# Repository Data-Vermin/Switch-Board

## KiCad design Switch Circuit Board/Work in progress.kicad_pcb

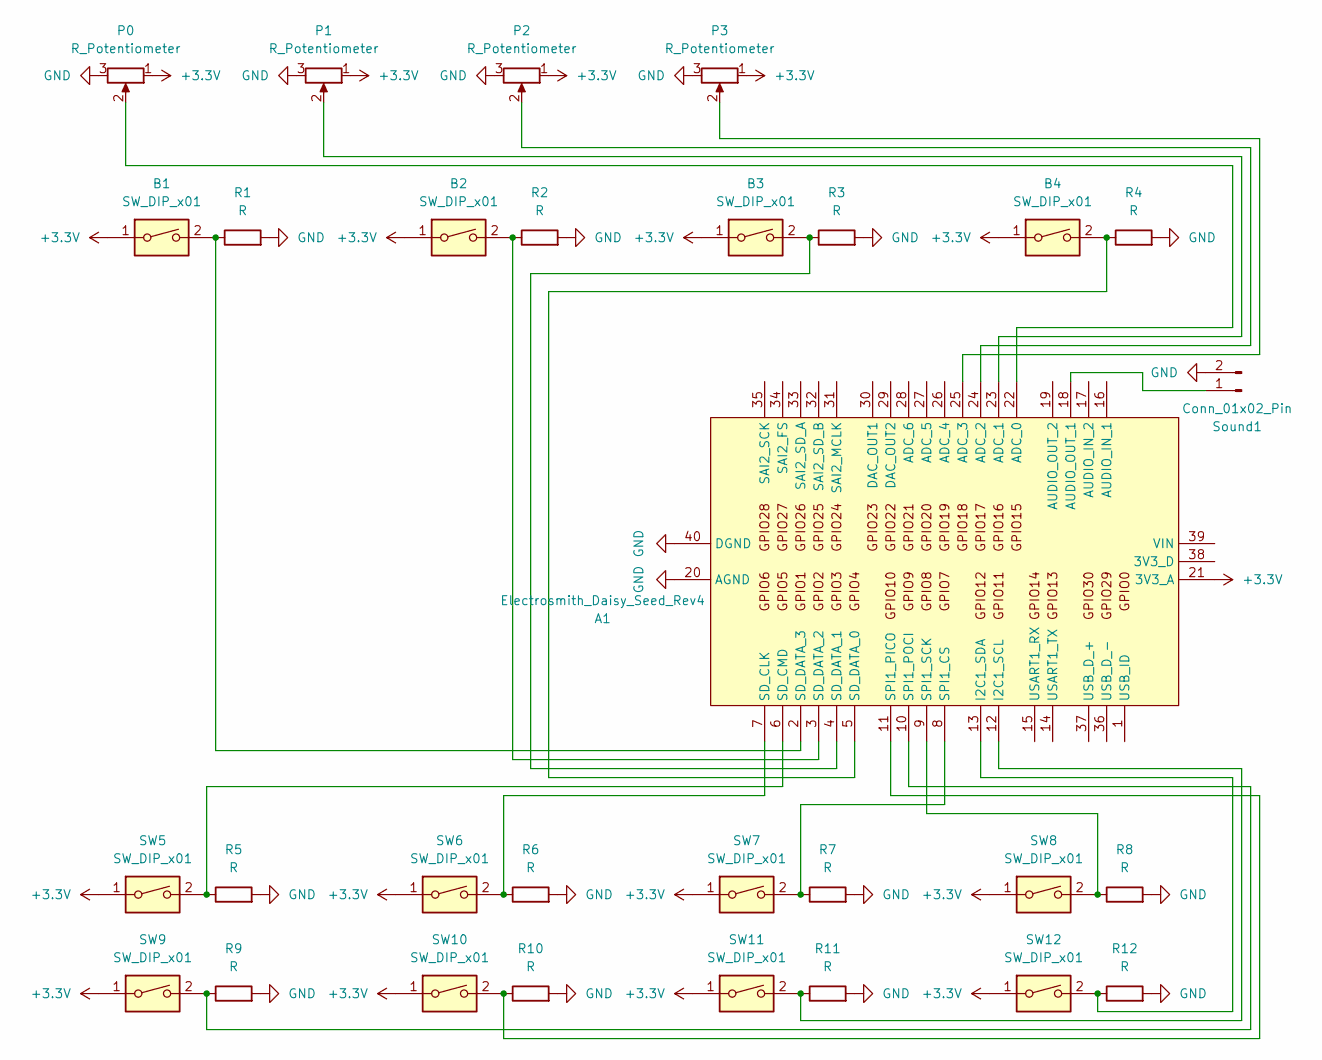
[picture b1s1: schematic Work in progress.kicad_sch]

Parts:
A1: Electrosmith_Daisy_Seed_Rev4; Electrosmith_Daisy_Seed
B1, B2, B3, B4: SW_DIP_x01; PinHeader_1x02_P2.54mm_Vertical
P0, P1, P2, P3: R_Potentiometer; PinHeader_1x03_P2.54mm_Vertical
R1, R2, R3, R4, R5, R6, R7, R8, R9, R10, R11, R12: R; R_Axial_DIN0204_L3.6mm_D1.6mm_P7.62mm_Horizontal
SW5, SW6, SW7, SW8, SW9, SW10, SW11, SW12: SW_DIP_x01; PinHeader_1x02_P2.54mm_Vertical
Sound1: Conn_01x02_Pin; PinHeader_1x02_P2.54mm_Vertical

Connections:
+3.3V: A1.21 (3V3_A), B1.1, B2.1, B3.1, B4.1, P0.1, P1.1, P2.1, P3.1, SW5.1, SW6.1, SW7.1, SW8.1, SW9.1, SW10.1, SW11.1, SW12.1
GND: A1.20 (AGND), A1.40 (DGND), P0.3, P1.3, P2.3, P3.3, R1.2, R2.2, R3.2, R4.2, R5.2, R6.2, R7.2, R8.2, R9.2, R10.2, R11.2, R12.2, Sound1.2
unnamed: A1.22 (ADC_0), P0.2
unnamed: A1.23 (ADC_1), P1.2
unnamed: A1.24 (ADC_2), P2.2
unnamed: A1.25 (ADC_3), P3.2
unnamed: A1.18 (AUDIO_OUT_1), Sound1.1
unnamed: A1.12 (I2C1_SCL), R11.1, SW11.2
unnamed: A1.13 (I2C1_SDA), R12.1, SW12.2
unnamed: A1.7 (SD_CLK), R6.1, SW6.2
unnamed: A1.6 (SD_CMD), R5.1, SW5.2
unnamed: A1.5 (SD_DATA_0), B4.2, R4.1
unnamed: A1.4 (SD_DATA_1), B3.2, R3.1
unnamed: A1.3 (SD_DATA_2), B2.2, R2.1
unnamed: A1.2 (SD_DATA_3), B1.2, R1.1
unnamed: A1.8 (SPI1_CS), R7.1, SW7.2
unnamed: A1.11 (SPI1_PICO), R10.1, SW10.2
unnamed: A1.10 (SPI1_POCI), R9.1, SW9.2
unnamed: A1.9 (SPI1_SCK), R8.1, SW8.2

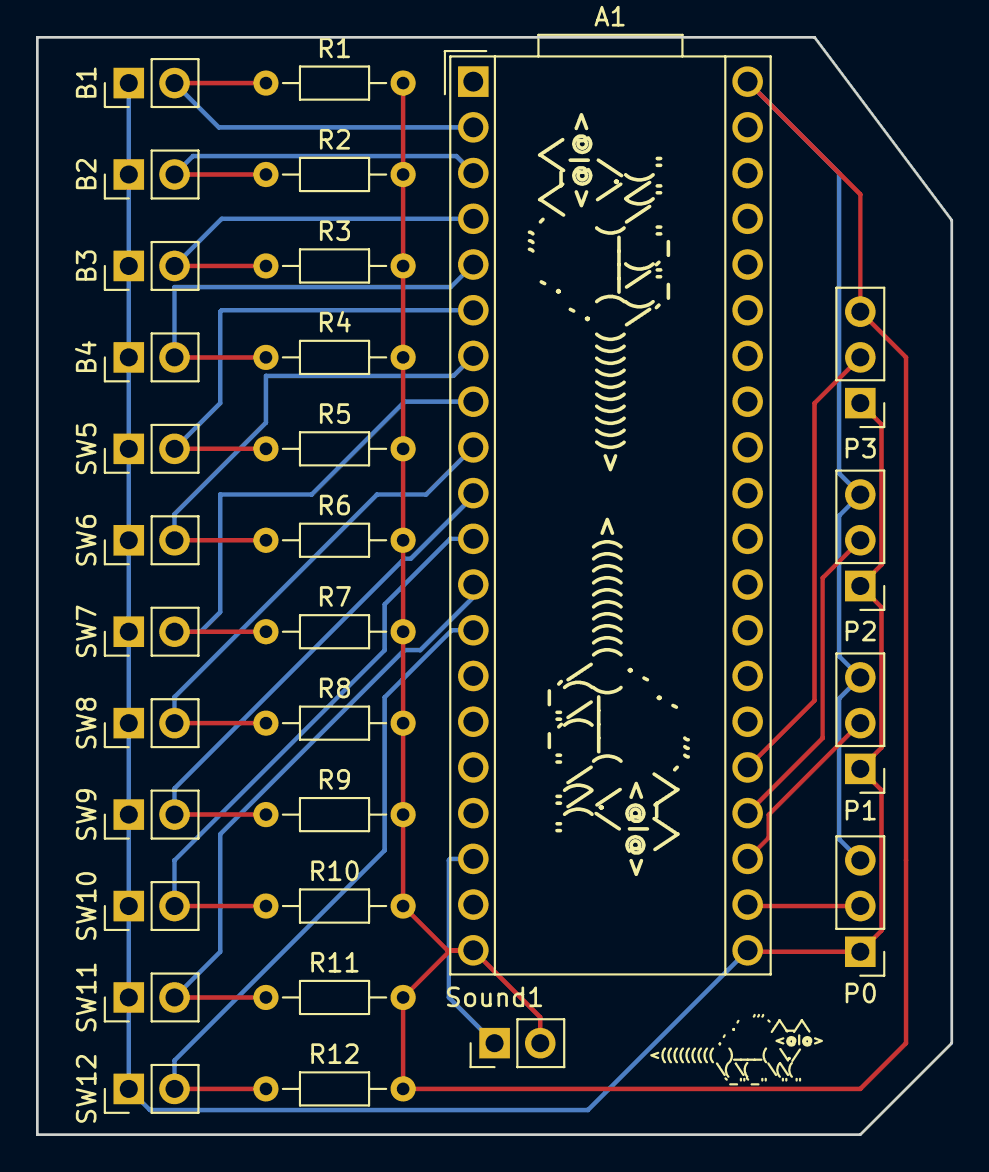
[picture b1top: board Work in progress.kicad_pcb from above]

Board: 2 copper layers, 50.8 x 61.0 mm, 30 parts (0 on the bottom side), 19 nets.
